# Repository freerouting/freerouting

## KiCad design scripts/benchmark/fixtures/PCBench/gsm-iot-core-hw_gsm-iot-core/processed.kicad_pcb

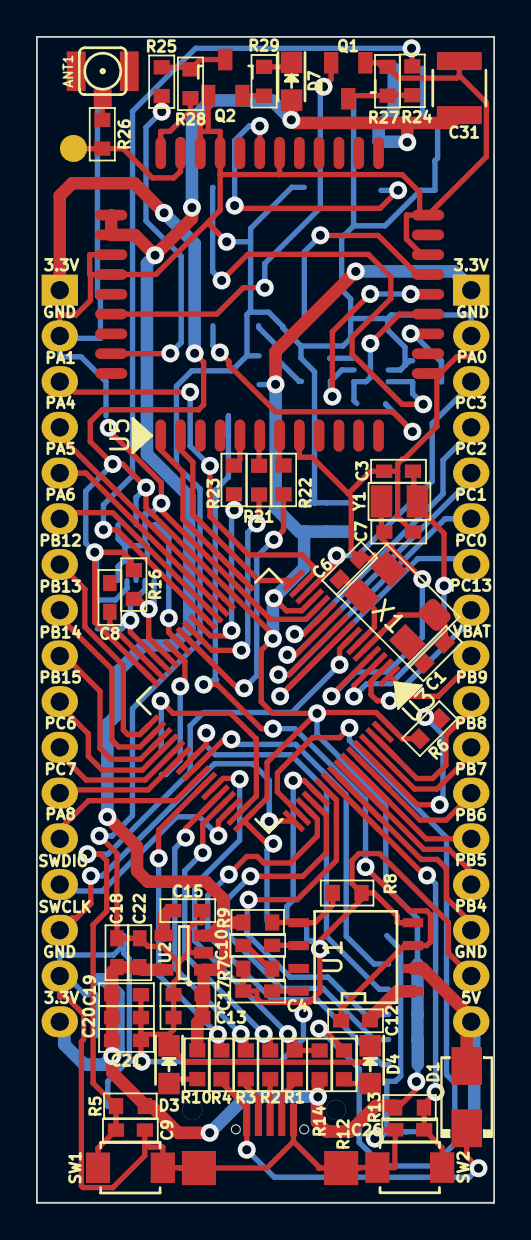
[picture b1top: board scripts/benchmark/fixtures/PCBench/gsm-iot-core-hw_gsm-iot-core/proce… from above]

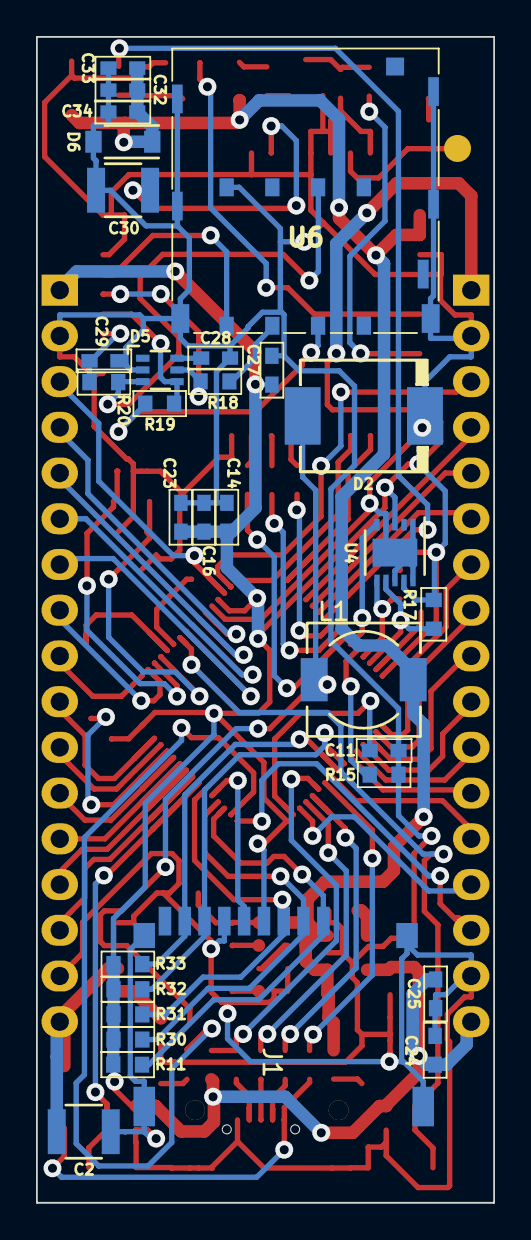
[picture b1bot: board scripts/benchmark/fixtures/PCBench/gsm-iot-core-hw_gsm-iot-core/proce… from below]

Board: 2 copper layers, 25.4 x 64.8 mm, 92 parts (31 on the bottom side), 93 nets.

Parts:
ANT1: ANTENNA; coaxial_u.fl-r-smt-1
C1, C6, C34: 10pF; C_0603
C2: 10uF/35V; C_1210
C3, C7: 15pF; C_0603
C4: 0.1uF; C_0603
C8, C11: 2.2uF; C_0603
C9, C18, C19, C20, C21, C23, C25, C26, C27, C28: 100nF; C_0603
C10: 4.7nF; C_0603
C12, C15: 10nF; C_0603
C13: 47uF; C_0603
C14, C16, C24: 4.7uF; C_0603
C17, C22, C32: 10uF; C_0603
C29: 22pF; C_0603
C30, C31: 100uF; C_1210
C33: 33pF; C_0603
CONN1: MICRO_USB; Micro_usb_B_smd
D1: SS34; do214ac
D2: MBRS340; do214ab
D3: Led_pwr; LED_0805
D4: PA15_LED; LED_0805
D5: SMF05C; SC-70-6
D6: zener 5.1v/500mW; SOD-123
D7: Led_SIM; LED_0805
J1: MICRO_SD_HINGE - Micro SD socket Push-Push A; MicroSD_Push-Push-A
L1: 4.7uH-2.2A; Choke_SMD_6.3x6.3_H3
P1, P2: CONN_01X17; Pin_Header_Straight_1x17
P3: Chip anten; point_test
Q1, Q2: 2SC1815; SOT-23
R1: DNF-1K; R_0603
R2, R3, R18, R19, R20: 22R; R_0603
R4, R21, R22, R23: 1K; R_0603
R5, R10: 10k; R_0603
R6, R13, R15, R29: 10K; R_0603
R7: 20k; R_0603
R8: 10k-1%; R_0603
R9: 33,6k-1%; R_0603
R11, R30, R31, R32, R33: 47K; R_0603
R12: 560R; R_0603
R14: 100k; R_0603
R16, R17, R24, R27: 4.7k; R_0603
R25, R28: 4k7; R_0603
R26: 0R; R_0603
SW1, SW2: SW_PUSH; SW_SPST_B3U-1000P-B
U1: MP2365DN; SOIC-8-N
U2: LP2985-50DBVR; SOT-23-5
U3: STM32F405RGTx; TQFP-64_10x10mm_Pitch0.5mm
U4: MMA7660; DFN-10-1EP_3x3mm_Pitch0.5mm
U5: SIM800C
U6: SIM HOLD - PPSS-6P; 115I-AEAA
X1: CRYSTAL-24M; Crystal_SMD_5032_4Pads
Y1: 32.768MHz; crystal_smd_32.768_2Pin

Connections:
+3V3: C14.1, C16.1, C18.1, C19.1, C20.1, C21.1, C22.1, C23.1, C24.1, C25.1, C27.1, J1.4, P1.1, P1.17, P2.1, R5.1, R6.1, R11.2, R13.2, R14.1, R16.1, R17.1, R30.2, R31.2, R32.2, R33.2, U2.5, U3.13, U3.19, U3.32, U3.48, U3.64, U4.3, U4.9
+5V: C2.1, D1.1, P2.17, U1.2
/RST: C9.1, R5.2, SW1.2, U3.7
GND: C2.2, C3.2, C4.2, C6.2, C7.2, C9.2, C11.2, C13.2, C14.2, C15.2, C16.2, C17.2, C18.2, C19.2, C20.2, C21.2, C22.2, C23.2, C24.2, C25.2, C26.2, C27.2, C28.2, C29.2, C30.2, C31.2, C32.2, C33.2, C34.2, CONN1.5, CONN1.6, D2.2, D3.1, D4.1, D5.2, D6.2, J1.6, J1.10, J1.11, J1.12, P1.2, P1.16, P2.2, P2.16, Q1.1, Q2.1, R7.2, R8.2, R15.2, R27.1, R28.2, SW1.1, SW2.2, U1.4, U2.2, U3.12, U3.18, U4.1, U4.4, U4.8, U4.10, U4.11, U5.8, U5.13, U5.19, U5.21, U5.27, U5.30, U5.31, U5.33, U5.36, U5.37, U6.5, X1.4
GSM_ANT: P3.1, R26.1, U5.32
unnamed: ANT1.1, R26.2
unnamed: C1.2, U3.5, X1.1
unnamed: C3.1, U3.3, Y1.1
unnamed: C4.1, U1.8
unnamed: C6.1, U3.6, X1.3
unnamed: C7.1, U3.4, Y1.2
unnamed: C8.1, U3.31
unnamed: C10.1, U1.6
unnamed: C10.2, R7.1
unnamed: C11.1, U3.47
unnamed: C12.1, D2.1, L1.1, U1.3
unnamed: C12.2, U1.1
unnamed: C15.1, U2.4
unnamed: C28.1, D5.6
unnamed: C30.1, U5.28
unnamed: CONN1.1, D1.2, R4.1
unnamed: CONN1.2, R3.1
unnamed: CONN1.3, R2.1
unnamed: CONN1.4, R1.1
unnamed: D3.2, R10.1
unnamed: D4.2, R12.2
unnamed: D5.3, R20.2, U6.7
unnamed: D7.1, R29.1
unnamed: Q1.3, R24.1, R27.2
unnamed: Q2.2, R29.2
unnamed: Q2.3, R25.1, R28.1
unnamed: R6.2, U3.60
unnamed: R8.1, R9.2, U1.5
unnamed: R15.1, U3.28
unnamed: R18.1, U6.2
unnamed: R19.1, U6.3
unnamed: R21.2, U5.6
unnamed: R22.2, U5.7
unnamed: R23.2, U5.5
PA0: P2.3, U3.14
PA1: P1.3, U3.15
PA4: P1.4, U3.20
PA5: P1.5, U3.21
PA6: P1.6, U3.22
PA7_PWRKEY: R24.2, U3.23
PA8: P1.13, U3.41
PA9_VBUS: R4.2, U3.42
PA10_ID: R1.2, R14.2, U3.43
PA11_DM: R3.2, U3.44
PA12_DP: R2.2, U3.45
PA13_SWDIO: P1.14, U3.46
PA14_SWCLK: P1.15, U3.49
PA15_LED: R12.1, U3.50
PB1: U3.27, U4.5
PB3_BUTTON: C26.1, R13.1, SW2.1, U3.55
PB4: P2.15, U3.56
PB5: P2.14, U3.57
PB6: P2.13, U3.58
PB7: P2.12, U3.59
PB8: P2.11, U3.61
PB9: P2.10, U3.62
PB10_SCL: R16.2, U3.29, U4.6
PB11_SDA: R17.2, U3.30, U4.7
PB12: P1.7, U3.33
PB13: P1.8, U3.34
PB14: P1.9, U3.35
PB15: P1.10, U3.36
PC0: P2.7, U3.8
PC1: P2.6, U3.9
PC2: P2.5, U3.10
PC3: P2.4, U3.11
PC6: P1.11, U3.37
PC7: P1.12, U3.38
PC8_SDIO_D0: J1.7, R32.1, U3.39
PC9_SDIO_D1: J1.8, R33.1, U3.40
PC10_SDIO_D2: J1.1, R11.1, U3.51
PC11_SDIO_D3: J1.2, R30.1, U3.52
PC12_SDIO_CK: J1.5, U3.53
PC13: P2.8, U3.2
PD2_SDIO_CMD: J1.3, R31.1, U3.54
SIM800C_CLK: D5.4, R19.2, U5.16
SIM800C_DATA: C29.1, R20.1, U5.15
SIM800C_DCD: R23.1, U3.24
SIM800C_DTR: R21.1, U3.25
SIM800C_NETLIGHT: R25.2, U5.41
SIM800C_PWRKEY: Q1.2, U5.39
SIM800C_RI: R22.1, U3.26
SIM800C_RST: D5.5, R18.2, U5.17
SIM800C_RXD: U3.16, U5.2
SIM800C_TXD: U3.17, U5.1
SIM800C_VDD: U5.18, U6.1
VBAT: P2.9, U3.1
VDD: C13.1, C17.1, C31.1, C32.1, C33.1, C34.1, D6.1, D7.2, L1.2, R9.1, R10.2, U2.1, U2.3, U5.34, U5.35

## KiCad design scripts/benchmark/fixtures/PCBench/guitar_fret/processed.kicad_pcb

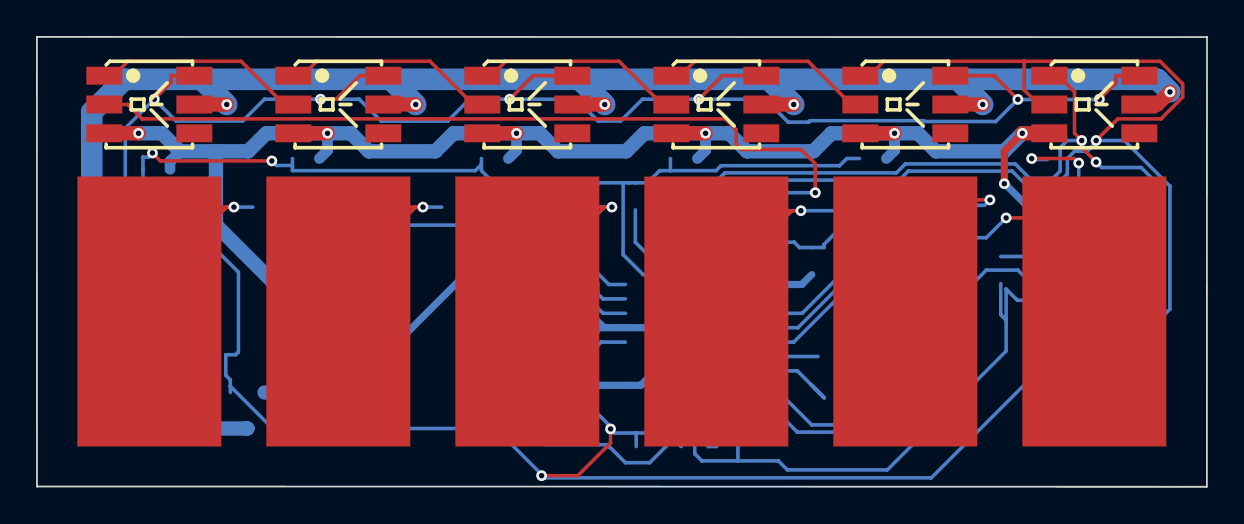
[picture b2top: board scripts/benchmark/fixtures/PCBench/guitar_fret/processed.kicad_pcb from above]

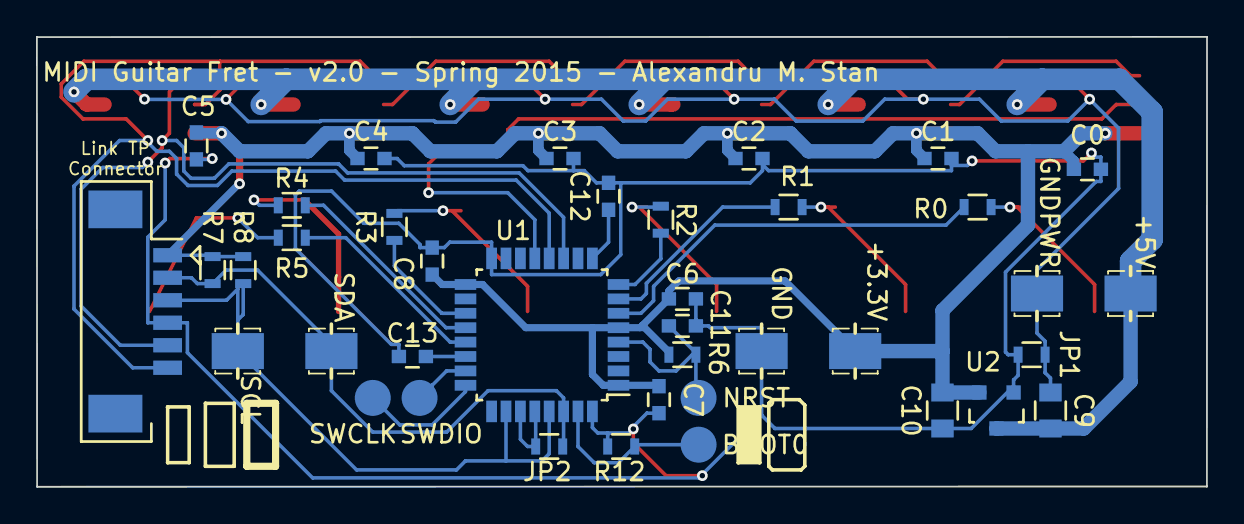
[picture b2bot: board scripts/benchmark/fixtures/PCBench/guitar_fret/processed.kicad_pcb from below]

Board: 2 copper layers, 65.0 x 25.0 mm, 51 parts (39 on the bottom side), 32 nets.

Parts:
C0, C1, C2, C3, C4, C5, C6, C7, C8, C11: 100nF; C_0603
C9, C10: 22uF; C_0805
C12, C13: 47nF; C_0603
J1: +5V; IDC-1x1
J2: GNDPWR; IDC-1x1
J3: +3.3V; IDC-1x1
J4: GND; IDC-1x1
J5: SDA; IDC-1x1
J6: SCL; IDC-1x1
J7: BOOT0; pad-2mm-round
J8: NRST; pad-2mm-round
J9: SWDIO; pad-2mm-round
J10: CONN_01X06; Connector_Molex_PicoBlade_53261-0671
J11: SWCLK; pad-2mm-round
JP1: GNDPWR-GND; R_0603
JP2: SPI-CONNECTION; R_0603
LED0, LED1, LED2, LED3, LED4, LED5: WS2812; 5050-6pin
P0, P1, P2, P3, P4, P5: TOUCH; TP-8x15
R0, R1, R2, R3, R4, R5, R6, R12: 10k; R_0603
R7, R8: 4.7k; R_0603
U1: STM32F051K*T; LQFP-32_7x7mm_Pitch0.8mm
U2: AP2210N-3.3TRG1; SOT-23

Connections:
+3V3: C0.1, C1.1, C2.1, C3.1, C4.1, C5.1, C6.1, C7.1, C8.1, C10.1, J3.1, J10.1, LED0.3, LED1.3, LED2.3, LED3.3, LED4.3, LED5.3, R6.2, R7.1, R8.1, U1.1, U1.5, U1.17, U2.2
+5V: C9.1, J1.1, LED0.5, LED1.5, LED2.5, LED3.5, LED4.5, LED5.5, U2.3
/BOOT0: J7.1, R12.2, U1.31
/BUTTON: J10.6, LED4.1, LED5.2, U1.12
/CG1: C12.1, U1.9
/CG4: C13.1, U1.22
/LED0: LED0.2, U1.13
/LED1: LED0.1, LED1.2
/LED2: LED1.1, LED2.2
/LED3: LED2.1, LED3.2
/LED4: LED3.1, LED4.2
/LED6: J10.5, LED5.1, U1.11
/MISO: JP2.1, U1.27, U1.28
/NRST: C11.1, J8.1, R6.1, U1.4
/P0: R0.1, U1.6
/P1: R1.1, U1.7
/P2: R2.1, U1.8
/P3: R3.1, U1.19
/P4: R4.1, U1.20
/P5: R5.1, U1.21
/SCK: J6.1, J10.3, R8.2, U1.26, U1.29
/SDA: J5.1, J10.2, JP2.2, R7.2, U1.30
/SWCLK: J11.1, U1.24
/SWDIO: J9.1, U1.23
GND: C0.2, C1.2, C2.2, C3.2, C4.2, C5.2, C6.2, C7.2, C8.2, C10.2, C11.2, C12.2, C13.2, J4.1, J10.4, JP1.2, R12.1, U1.16, U1.32, U2.1
GNDPWR: C9.2, J2.1, JP1.1, LED0.6, LED1.6, LED2.6, LED3.6, LED4.6, LED5.6
unnamed: P0.1, R0.2
unnamed: P1.1, R1.2
unnamed: P2.1, R2.2
unnamed: P3.1, R3.2
unnamed: P4.1, R4.2
unnamed: P5.1, R5.2

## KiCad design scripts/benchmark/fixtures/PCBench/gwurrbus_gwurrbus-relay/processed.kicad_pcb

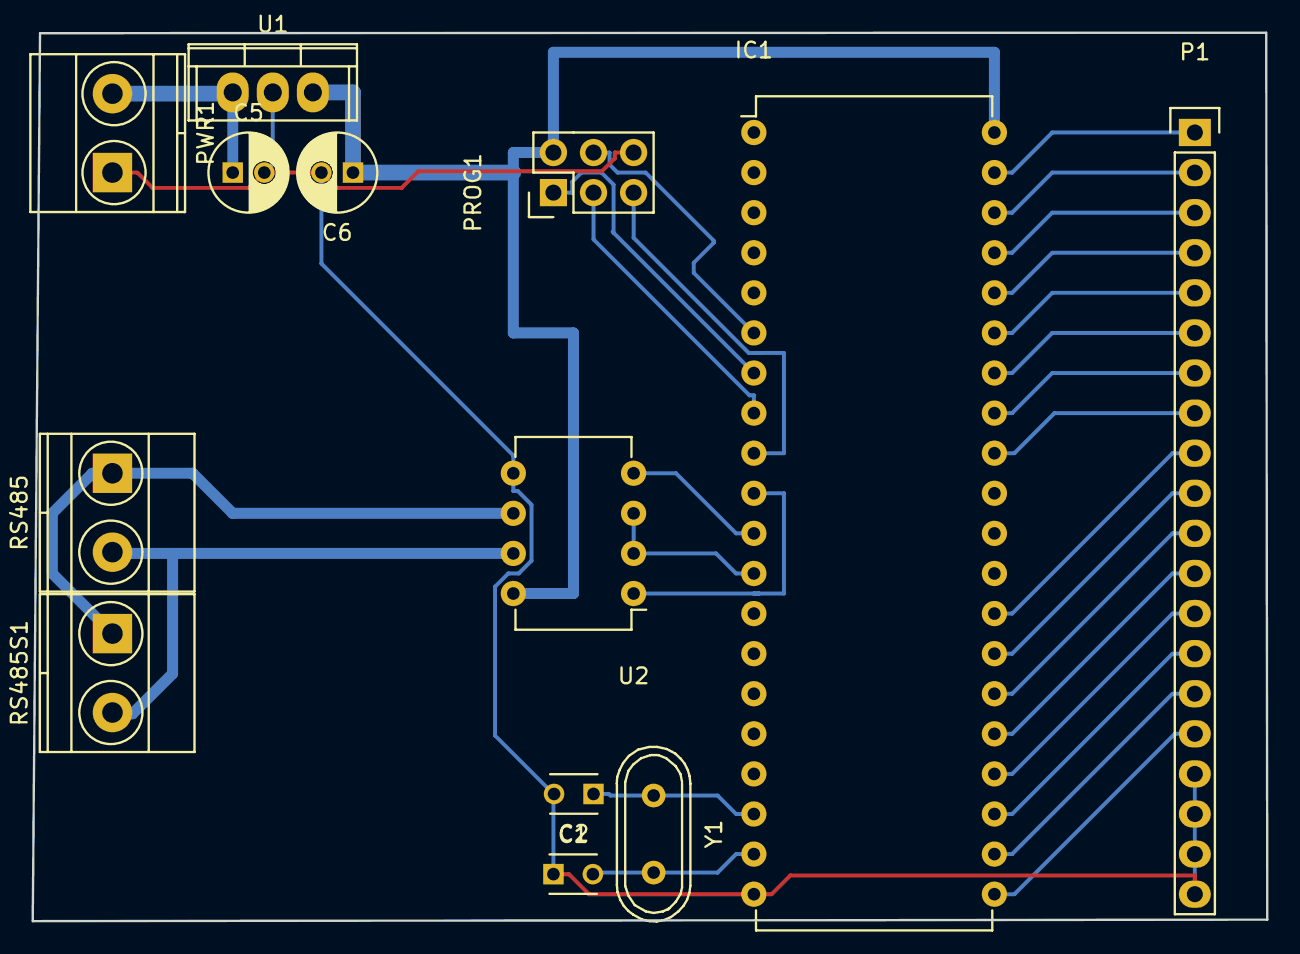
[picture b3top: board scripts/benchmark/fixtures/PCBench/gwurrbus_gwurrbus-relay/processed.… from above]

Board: 2 copper layers, 78.2 x 56.3 mm, 13 parts (0 on the bottom side), 30 nets.

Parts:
C1, C2: C_Small; C_Disc_D3_P2.5
C5, C6: 10uf; C_Radial_D5_L11_P2
IC1: AT90S8515-P; DIP-40_W15.24mm
P1: CONN_01X20; Pin_Header_Straight_1x20
PROG1: CONN_02X03; Pin_Header_Straight_2x03
PWR1: CONN_01X02; TerminalBlock_Pheonix_MKDS1.5-2pol
RS485, RS485S1: CONN_01X02; TerminalBlock_Pheonix_MKDS1.5-2pol
U1: LM7805CT; TO-220
U2: SP3485CP; DIP-8_W7.62mm
Y1: 16mhz; Crystal_HC49-U_Vertical

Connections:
+5V: C6.1, IC1.40, PROG1.2, U1.3, U2.8
+BATT: C5.1, PWR1.2, U1.1
/MISO: IC1.7, PROG1.1
/MOSI: IC1.6, PROG1.4
/O1: IC1.39, P1.1
/O2: IC1.38, P1.2
/O3: IC1.37, P1.3
/O4: IC1.36, P1.4
/O5: IC1.35, P1.5
/O6: IC1.34, P1.6
/O7: IC1.33, P1.7
/O8: IC1.32, P1.8
/O9: IC1.21, P1.16
/O10: IC1.22, P1.15
/O11: IC1.23, P1.14
/O12: IC1.24, P1.13
/O13: IC1.25, P1.12
/O14: IC1.26, P1.11
/O15: IC1.27, P1.10
/O16: IC1.28, P1.9
/RESET: IC1.9, PROG1.5
/SCK: IC1.8, PROG1.3
Earth: C1.1, C2.2, C5.2, C6.2, IC1.20, P1.17, P1.18, P1.19, P1.20, PROG1.6, PWR1.1, U1.2, U2.5
unnamed: C1.2, IC1.19, Y1.2
unnamed: C2.1, IC1.18, Y1.1
unnamed: IC1.10, U2.1
unnamed: IC1.11, U2.4
unnamed: IC1.12, U2.2, U2.3
unnamed: RS485.1, RS485S1.1, U2.6
unnamed: RS485.2, RS485S1.2, U2.7
